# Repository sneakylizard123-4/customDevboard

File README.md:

# customDevboard
custom devboard made with RP 2040 in 30x30 flight controller size

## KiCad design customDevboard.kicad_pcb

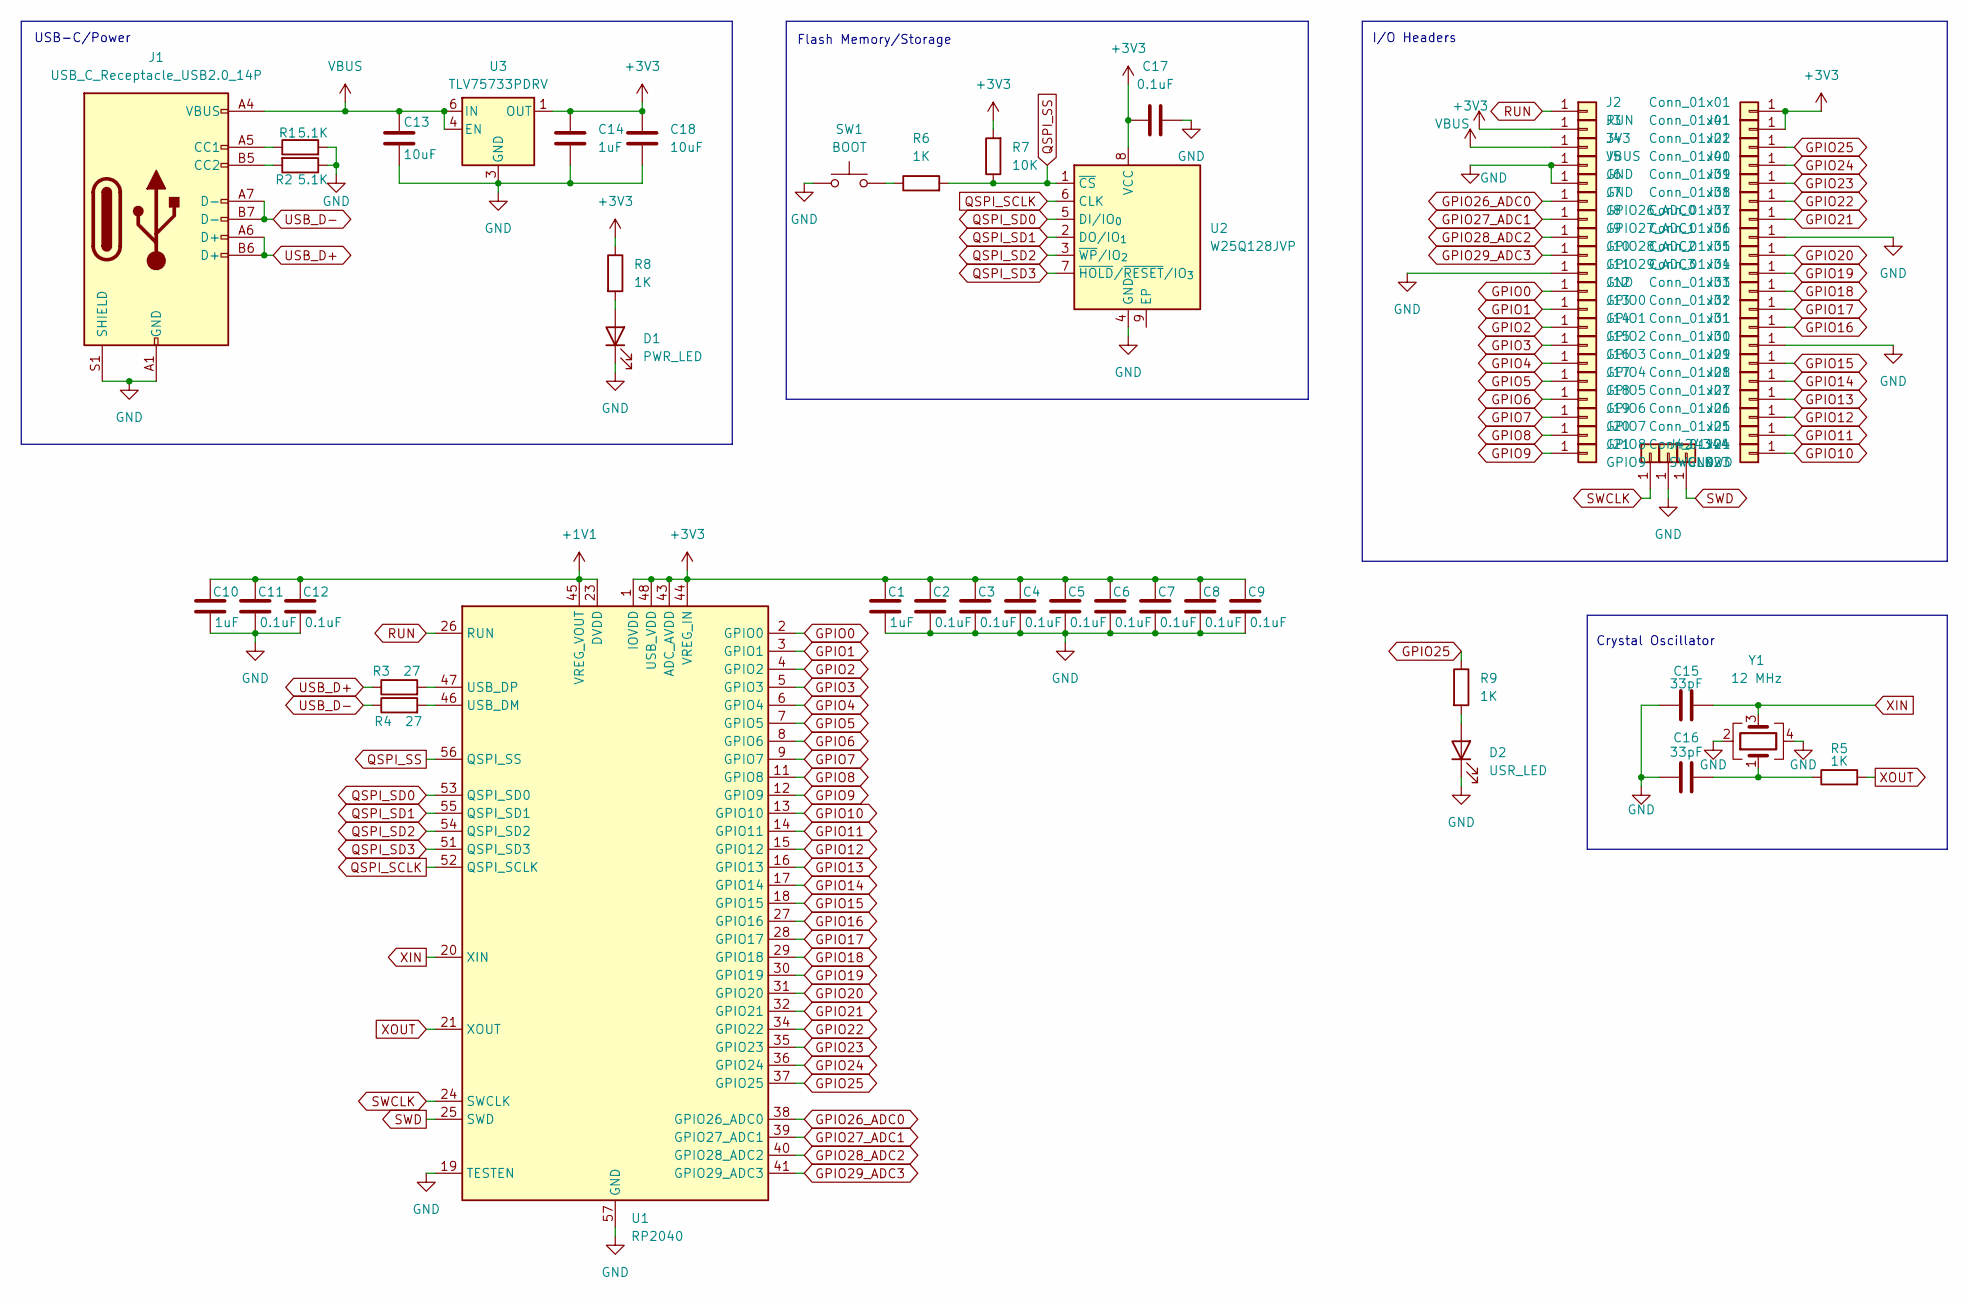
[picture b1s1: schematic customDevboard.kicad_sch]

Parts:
C1, C10, C14: 1uF; C_0402_1005Metric
C2, C3, C4, C5, C6, C7, C8, C9, C11, C12, C17: 0.1uF; C_0402_1005Metric
C13, C18: 10uF; C_0402_1005Metric
C15, C16: 33pF; C_0402_1005Metric
D1: PWR_LED; LED_0402_1005Metric
D2: USR_LED; LED_0402_1005Metric
J1: USB_C_Receptacle_USB2.0_14P; USB_C_Receptacle_HRO_TYPE-C-31-M-12
J2: RUN; SolderWirePad_1x01_SMD_1x2mm
J3: 3V3; SolderWirePad_1x01_SMD_1x2mm
J4: VBUS; SolderWirePad_1x01_SMD_1x2mm
J5, J6, J11, J43: GND; SolderWirePad_1x01_SMD_1x2mm
J7: GPIO26_ADC0; SolderWirePad_1x01_SMD_1x2mm
J8: GPIO27_ADC1; SolderWirePad_1x01_SMD_1x2mm
J9: GPIO28_ADC2; SolderWirePad_1x01_SMD_1x2mm
J10: GPIO29_ADC3; SolderWirePad_1x01_SMD_1x2mm
J12: GPIO0; SolderWirePad_1x01_SMD_1x2mm
J13: GPIO1; SolderWirePad_1x01_SMD_1x2mm
J14: GPIO2; SolderWirePad_1x01_SMD_1x2mm
J15: GPIO3; SolderWirePad_1x01_SMD_1x2mm
J16: GPIO4; SolderWirePad_1x01_SMD_1x2mm
J17: GPIO5; SolderWirePad_1x01_SMD_1x2mm
J18: GPIO6; SolderWirePad_1x01_SMD_1x2mm
J19: GPIO7; SolderWirePad_1x01_SMD_1x2mm
J20: GPIO8; SolderWirePad_1x01_SMD_1x2mm
J21: GPIO9; SolderWirePad_1x01_SMD_1x2mm
J22, J23, J24, J25, J26, J27, J28, J29, J30, J31, J32, J33, J34, J35, J36, J37, J38, J39, J40, J41: Conn_01x01; SolderWirePad_1x01_SMD_1x2mm
J42: SWCLK; SolderWirePad_1x01_SMD_1x2mm
J44: SWD; SolderWirePad_1x01_SMD_1x2mm
R1, R2: 5.1K; R_0402_1005Metric
R3, R4: 27; R_0402_1005Metric
R5, R6, R8, R9: 1K; R_0402_1005Metric
R7: 10K; R_0402_1005Metric
SW1: BOOT; SW_Push_SPST_NO_Alps_SKRK
U1: RP2040; QFN-56-1EP_7x7mm_P0.4mm_EP3.2x3.2mm
U2: W25Q128JVP; WSON-8-1EP_6x5mm_P1.27mm_EP3.4x4.3mm
U3: TLV75733PDRV; WSON-6-1EP_2x2mm_P0.65mm_EP1x1.6mm
Y1: 12 MHz; Crystal_SMD_3225-4Pin_3.2x2.5mm

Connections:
+1V1: C10.1, C11.1, C12.1, U1.23 (DVDD), U1.45 (VREG_VOUT), U1.50 (DVDD)
+3V3: C1.1, C2.1, C3.1, C4.1, C5.1, C6.1, C7.1, C8.1, C9.1, C14.1, C17.1, C18.1, J3.1, J22.1, J41.1, R7.2, R8.1, U1.1 (IOVDD), U1.10 (IOVDD), U1.22 (IOVDD), U1.33 (IOVDD), U1.42 (IOVDD), U1.43 (ADC_AVDD), U1.44 (VREG_IN), U1.48 (USB_VDD), U1.49 (IOVDD), U2.8 (VCC), U3.1 (OUT)
GND: C1.2, C2.2, C3.2, C4.2, C5.2, C6.2, C7.2, C8.2, C9.2, C10.2, C11.2, C12.2, C13.2, C14.2, C15.1, C16.1, C17.2, C18.2, D1.1 (K), D2.1 (K), J1.A1 (GND), J1.A12 (GND), J1.B1 (GND), J1.B12 (GND), J1.S1 (SHIELD), J5.1, J6.1, J11.1, J29.1, J35.1, J43.1, R1.2, R2.1, SW1.1, U1.19 (TESTEN), U1.57 (GND), U2.4 (GND), U3.3 (GND), U3.7 (GND), Y1.2, Y1.4
GPIO0: J12.1, U1.2 (GPIO0)
GPIO1: J13.1, U1.3 (GPIO1)
GPIO2: J14.1, U1.4 (GPIO2)
GPIO3: J15.1, U1.5 (GPIO3)
GPIO4: J16.1, U1.6 (GPIO4)
GPIO5: J17.1, U1.7 (GPIO5)
GPIO6: J18.1, U1.8 (GPIO6)
GPIO7: J19.1, U1.9 (GPIO7)
GPIO8: J20.1, U1.11 (GPIO8)
GPIO9: J21.1, U1.12 (GPIO9)
GPIO10: J23.1, U1.13 (GPIO10)
GPIO11: J24.1, U1.14 (GPIO11)
GPIO12: J25.1, U1.15 (GPIO12)
GPIO13: J26.1, U1.16 (GPIO13)
GPIO14: J27.1, U1.17 (GPIO14)
GPIO15: J28.1, U1.18 (GPIO15)
GPIO16: J30.1, U1.27 (GPIO16)
GPIO17: J31.1, U1.28 (GPIO17)
GPIO18: J32.1, U1.29 (GPIO18)
GPIO19: J33.1, U1.30 (GPIO19)
GPIO20: J34.1, U1.31 (GPIO20)
GPIO21: J36.1, U1.32 (GPIO21)
GPIO22: J37.1, U1.34 (GPIO22)
GPIO23: J38.1, U1.35 (GPIO23)
GPIO24: J39.1, U1.36 (GPIO24)
GPIO25: J40.1, R9.1, U1.37 (GPIO25)
GPIO26_ADC0: J7.1, U1.38 (GPIO26_ADC0)
GPIO27_ADC1: J8.1, U1.39 (GPIO27_ADC1)
GPIO28_ADC2: J9.1, U1.40 (GPIO28_ADC2)
GPIO29_ADC3: J10.1, U1.41 (GPIO29_ADC3)
unnamed: C16.2, R5.1, Y1.1
unnamed: D1.2 (A), R8.2
unnamed: D2.2 (A), R9.2
unnamed: J1.A5 (CC1), R1.1
unnamed: J1.B5 (CC2), R2.2
unnamed: R6.1, SW1.2
unnamed: R4.2, U1.46 (USB_DM)
unnamed: R3.2, U1.47 (USB_DP)
QSPI_SCLK: U1.52 (QSPI_SCLK), U2.6 (CLK)
QSPI_SD0: U1.53 (QSPI_SD0), U2.5 (DI/IO_{0})
QSPI_SD1: U1.55 (QSPI_SD1), U2.2 (DO/IO_{1})
QSPI_SD2: U1.54 (QSPI_SD2), U2.3 (~WP/IO_{2})
QSPI_SD3: U1.51 (QSPI_SD3), U2.7 (~HOLD/~RESET/IO_{3})
QSPI_SS: R6.2, R7.1, U1.56 (QSPI_SS), U2.1 (~CS)
RUN: J2.1, U1.26 (RUN)
SWCLK: J42.1, U1.24 (SWCLK)
SWD: J44.1, U1.25 (SWD)
USB_D+: J1.A6 (D+), J1.B6 (D+), R3.1
USB_D-: J1.A7 (D-), J1.B7 (D-), R4.1
VBUS: C13.1, J1.A4 (VBUS), J1.A9 (VBUS), J1.B4 (VBUS), J1.B9 (VBUS), J4.1, U3.4 (EN), U3.6 (IN)
XIN: C15.2, U1.20 (XIN), Y1.3
XOUT: R5.2, U1.21 (XOUT)

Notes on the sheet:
USB-C/Power
Crystal Oscillator
Flash Memory/Storage
I/O Headers

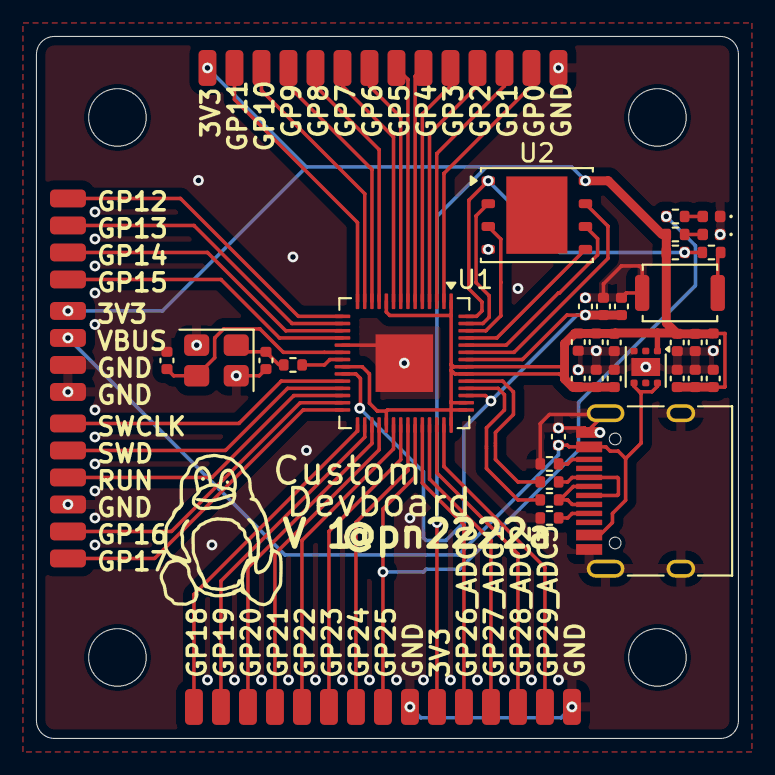
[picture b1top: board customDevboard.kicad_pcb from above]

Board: 2 copper layers, 39.0 x 39.0 mm, 78 parts (0 on the bottom side), 55 nets.

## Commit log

2025-12-12 It works! I hope
2025-12-13 V1 testing release
2025-12-15 gerbers
2025-12-15 fixed mounting hole size
2025-12-15 fixed mounting holes
2025-12-16 Add image to README for custom devboard
    Added an image to the README for better visualization.
2025-12-16 update pcb with mounting holes
2025-12-19 step file
2025-12-19 recompile
2025-12-19 Add additional image to README
    jlcpcb cart image
2025-12-19 Update images in README.md
    Updated images in the README to reflect new screenshots.
2025-12-24 update pcb
2025-12-24 use lead free hasl finish
2025-12-24 use lead free hasl finish
    Replaced an image in the README with a new one.
2025-12-24 Update image in README.md
    Replaced an image in the README with a new one.
2025-12-31 optimise
